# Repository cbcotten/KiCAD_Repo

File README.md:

# KiCAD_Repo
Custom libraries and projects using KiCAD

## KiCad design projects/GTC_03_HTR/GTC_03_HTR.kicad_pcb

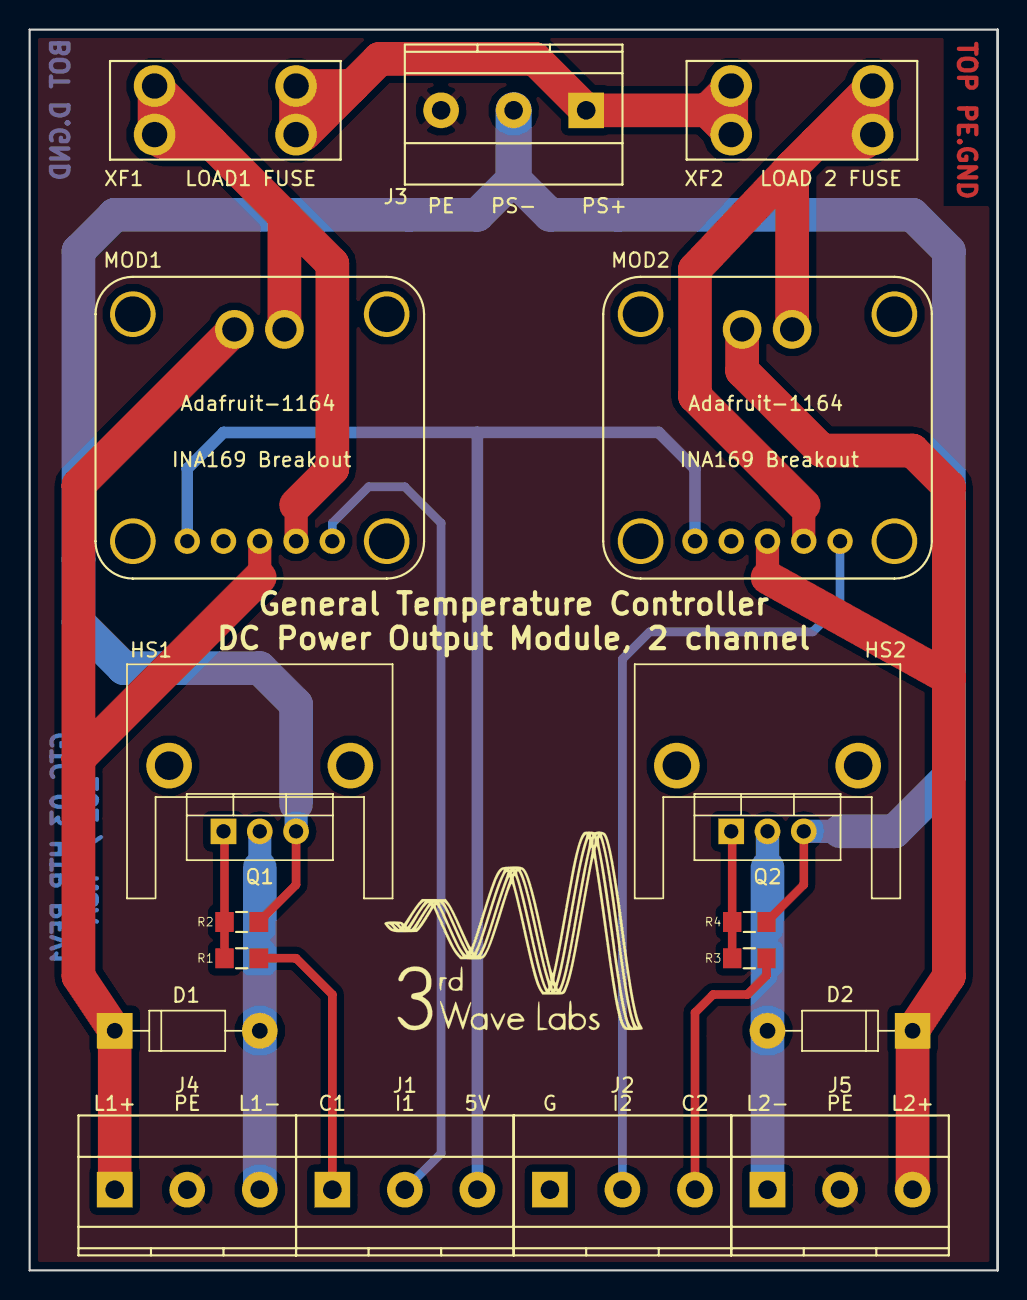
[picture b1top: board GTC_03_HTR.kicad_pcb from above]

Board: 2 copper layers, 67.8 x 86.9 mm, 20 parts (0 on the bottom side), 17 nets.

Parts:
D1, D2: D_1N4002_LargePad; D_DO-41_Horiz_Pitch10.16_Pad2.5
ENCLOSURE1: Bud_Industries_DMB-4772; Enclosure-DMB-4772
HS1, HS2: HeatSink_WV-T220-101E; Heatsink_Wx-T220-101E
J1, J2, J3, J4, J5: TB_PhxContact_MKDS-1.5-3-5.08; TB_PhxCon_MKDS-1.5-3-5.08
MOD1, MOD2: Adafruit_INA169_0291; Adafruit-1164_INA169_0291
Q1, Q2: MOSFET_STP40NF10L; TO-220_Vertical
R1, R3: RES-1000-077_150Ohm; R0805
R2, R4: RES-1000-121_10K; R0805
XF1, XF2: FuseHolder_MiniBlade_3568; Fuse_Holder_Keystone_3568

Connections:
/5V: J1.3, MOD1.1, MOD2.1
/CHASSIS: J3.3, J4.2, J5.2
/CONTROL1: J1.1, R1.1
/CONTROL2: J2.3, R3.1
/FUSE_1/FUSE_OUT: MOD1.4, MOD1.6, XF1.2
/FUSE_2/FUSE_OUT: MOD2.4, MOD2.6, XF2.2
/GND: J2.1, MOD1.2, MOD2.2
/HV+: J3.1, XF1.1, XF2.1
/HV-: J3.2, Q1.3, Q2.3, R2.2, R4.2
/ISENSE1: J1.2, MOD1.5
/ISENSE2: J2.2, MOD2.5
/LOAD1+: D1.1, J4.1, MOD1.3, MOD1.7
/LOAD1-: D1.2, J4.3, Q1.2
/LOAD2+: D2.1, J5.3, MOD2.3, MOD2.7
/LOAD2-: D2.2, J5.1, Q2.2
unnamed: Q1.1, R1.2, R2.1
unnamed: Q2.1, R3.2, R4.1

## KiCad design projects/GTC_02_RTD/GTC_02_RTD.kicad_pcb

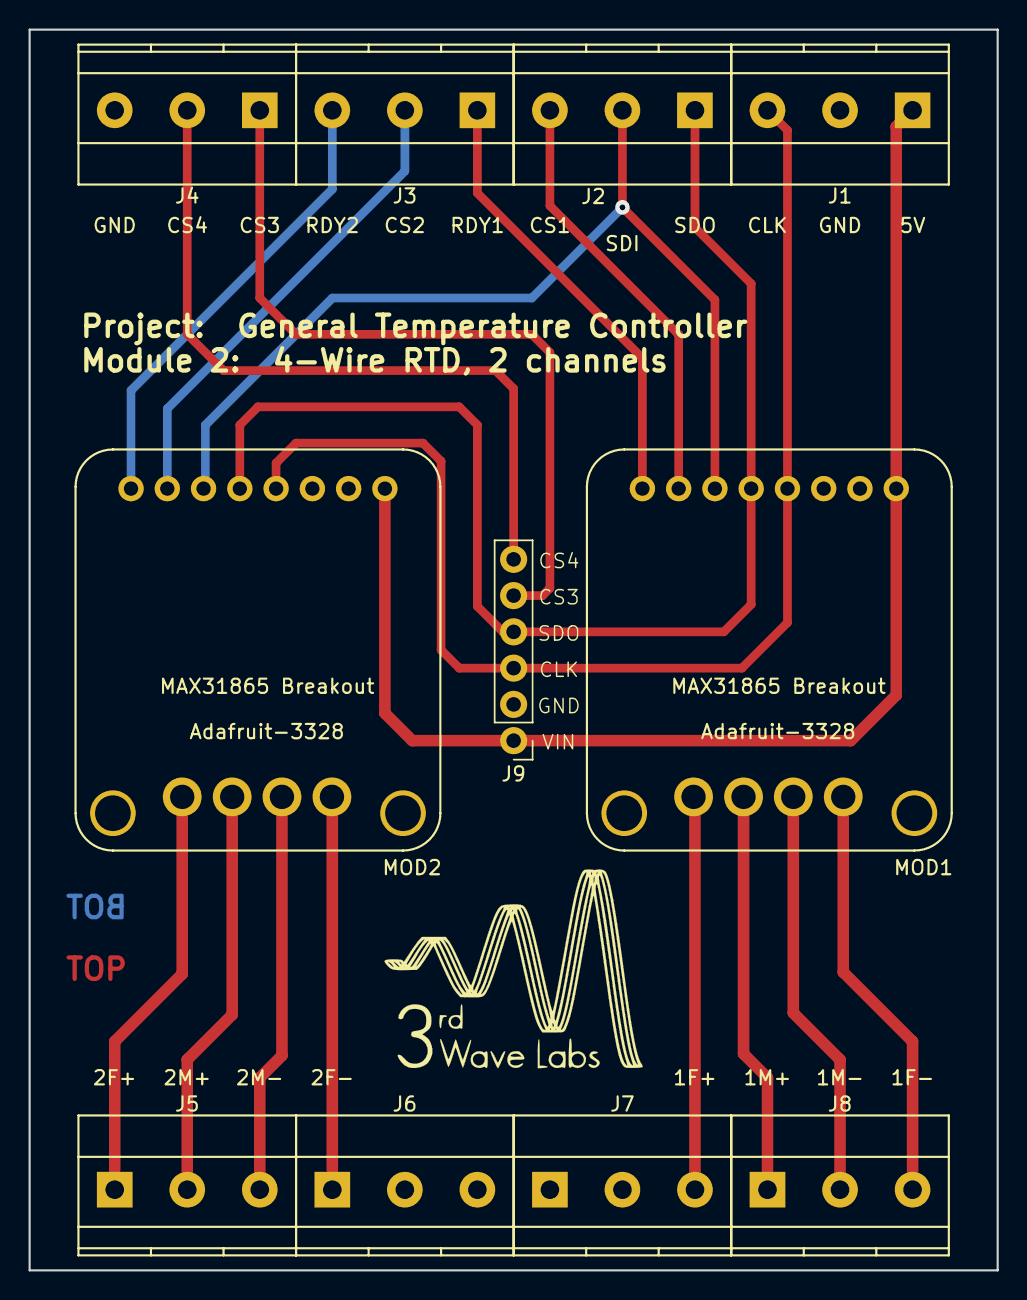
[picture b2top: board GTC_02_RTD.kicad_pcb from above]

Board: 2 copper layers, 67.8 x 86.9 mm, 12 parts (0 on the bottom side), 20 nets.

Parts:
ENCLOSURE1: Bud_Industries_DMB-4772; Enclosure-DMB-4772
J1, J2, J3, J4, J5, J6, J7, J8: TB_PhxContact_MKDS-1.5-3-5.08; TB_PhxCon_MKDS-1.5-3-5.08
J9: Pin_Header_Straight_2.54mm_1x06; Pin_Header_Straight_1x06_Pitch2.54mm
MOD1, MOD2: Adafruit_MAX31865_0291; Adafruit-3328_MAX31865_0291

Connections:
CLK: J1.3, J9.3, MOD1.4, MOD2.4
CS1: J2.3, MOD1.7
CS2: J3.2, MOD2.7
CS3: J4.1, J9.5
CS4: J4.2, J9.6
GND: J1.2, J4.3, J9.2, MOD1.2, MOD2.2
HTR1_SHIELD: J6.2, J6.3, J7.1, J7.2
RDY1: J3.1, MOD1.8
RDY2: J3.3, MOD2.8
RTD1_F+: J7.3, MOD1.9
RTD1_F-: J8.3, MOD1.12
RTD1_M+: J8.1, MOD1.10
RTD1_M-: J8.2, MOD1.11
RTD2_F+: J5.1, MOD2.9
RTD2_F-: J6.1, MOD2.12
RTD2_M+: J5.2, MOD2.10
RTD2_M-: J5.3, MOD2.11
SDI: J2.2, MOD1.6, MOD2.6
SDO: J2.1, J9.4, MOD1.5, MOD2.5
VIN: J1.1, J9.1, MOD1.1, MOD2.1

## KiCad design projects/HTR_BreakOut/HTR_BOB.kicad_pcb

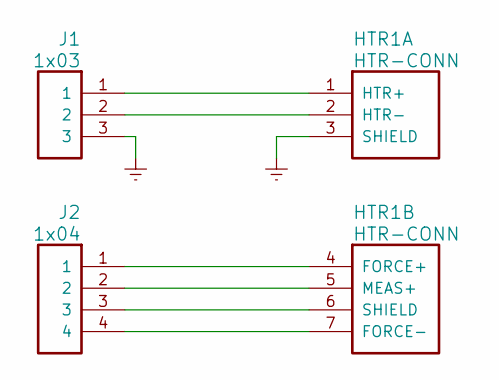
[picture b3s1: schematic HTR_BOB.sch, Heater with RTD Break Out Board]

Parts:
HTR1: HTR-CONN; Oasis_HeaterWithRTD_MillMax-0531
J1: 1x03; PhoenixContact_PTSM_0,5_3-HV-2,5-SMD
J2: 1x04; PhoenixContact_PTSM_0,5_4-HV-2,5-SMD

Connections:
Earth: HTR1.3 (SHIELD), J1.3
unnamed: HTR1.1 (HTR+), J1.1
unnamed: HTR1.2 (HTR-), J1.2
unnamed: HTR1.4 (FORCE+), J2.1
unnamed: HTR1.5 (MEAS+), J2.2
unnamed: HTR1.6 (SHIELD), J2.3
unnamed: HTR1.7 (FORCE-), J2.4

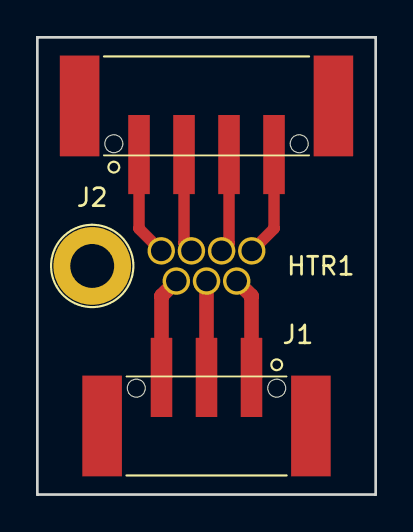
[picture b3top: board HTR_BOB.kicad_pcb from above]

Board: 2 copper layers, 18.8 x 25.4 mm, 3 parts (0 on the bottom side), 7 nets.

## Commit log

2017-03-24 Heater breakout board project
2017-04-11 freetronics library and CBC_Arduino library
2017-04-11 renamed files in KiPart folder
2017-06-28 Libraries, Footprints, and Project files for GTC
2017-06-28 deleted PAM project
2017-06-29 GTC_03_HTR revision 0
2017-06-30 GTC_SYSTEM_01 draft version
2017-06-30 GTC_SYSTEM_01 schem upate
2017-06-30 changed Cu text per fab house recommendation
2017-06-30 GTC_03_HTR_REV1, 3oz. Cu, 6/30/2017
2017-06-30 GTC_03_HTR_REV1, 1oz Cu, 6/30/2017
2017-06-30 GTC_SYSTEM_01, REV 1
2017-06-30 GTC_STSTEM_01 Rev1, release
2017-07-07 Revision 2
